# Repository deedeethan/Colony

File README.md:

Colony
======

**General Body Meeting: Thursdays at 5:30pm in WEH 5312**
- Mechanical: Saturdays 1pm in Roboclub
  - contact Jason Dynes (jdynes@andrew.cmu.edu)
- Electrical: Saturdays 1pm in Roboclub
  - contact Jess Chernak (jchernak@andrew.cmu.edu)
- Low Level: Saturdays 3:30pm in Roboclub
  - contact Tom Mullins (tmullins@andrew.cmu.edu)
- High Level: Thursdays after GBM (6:00pm) in WEH 5312
  - contact Tim Brown (twbrown@andrew.cmu.edu)

Contact: [aperley@andrew.cmu.edu](mailto:aperley@andrew.cmu.edu), [jchernak@andrew.cmu.edu](mailto:jchernak@andrew.cmu.edu)

[Wiki](https://github.com/CMU-Robotics-Club/Colony/wiki)
--------------------------------------------------------

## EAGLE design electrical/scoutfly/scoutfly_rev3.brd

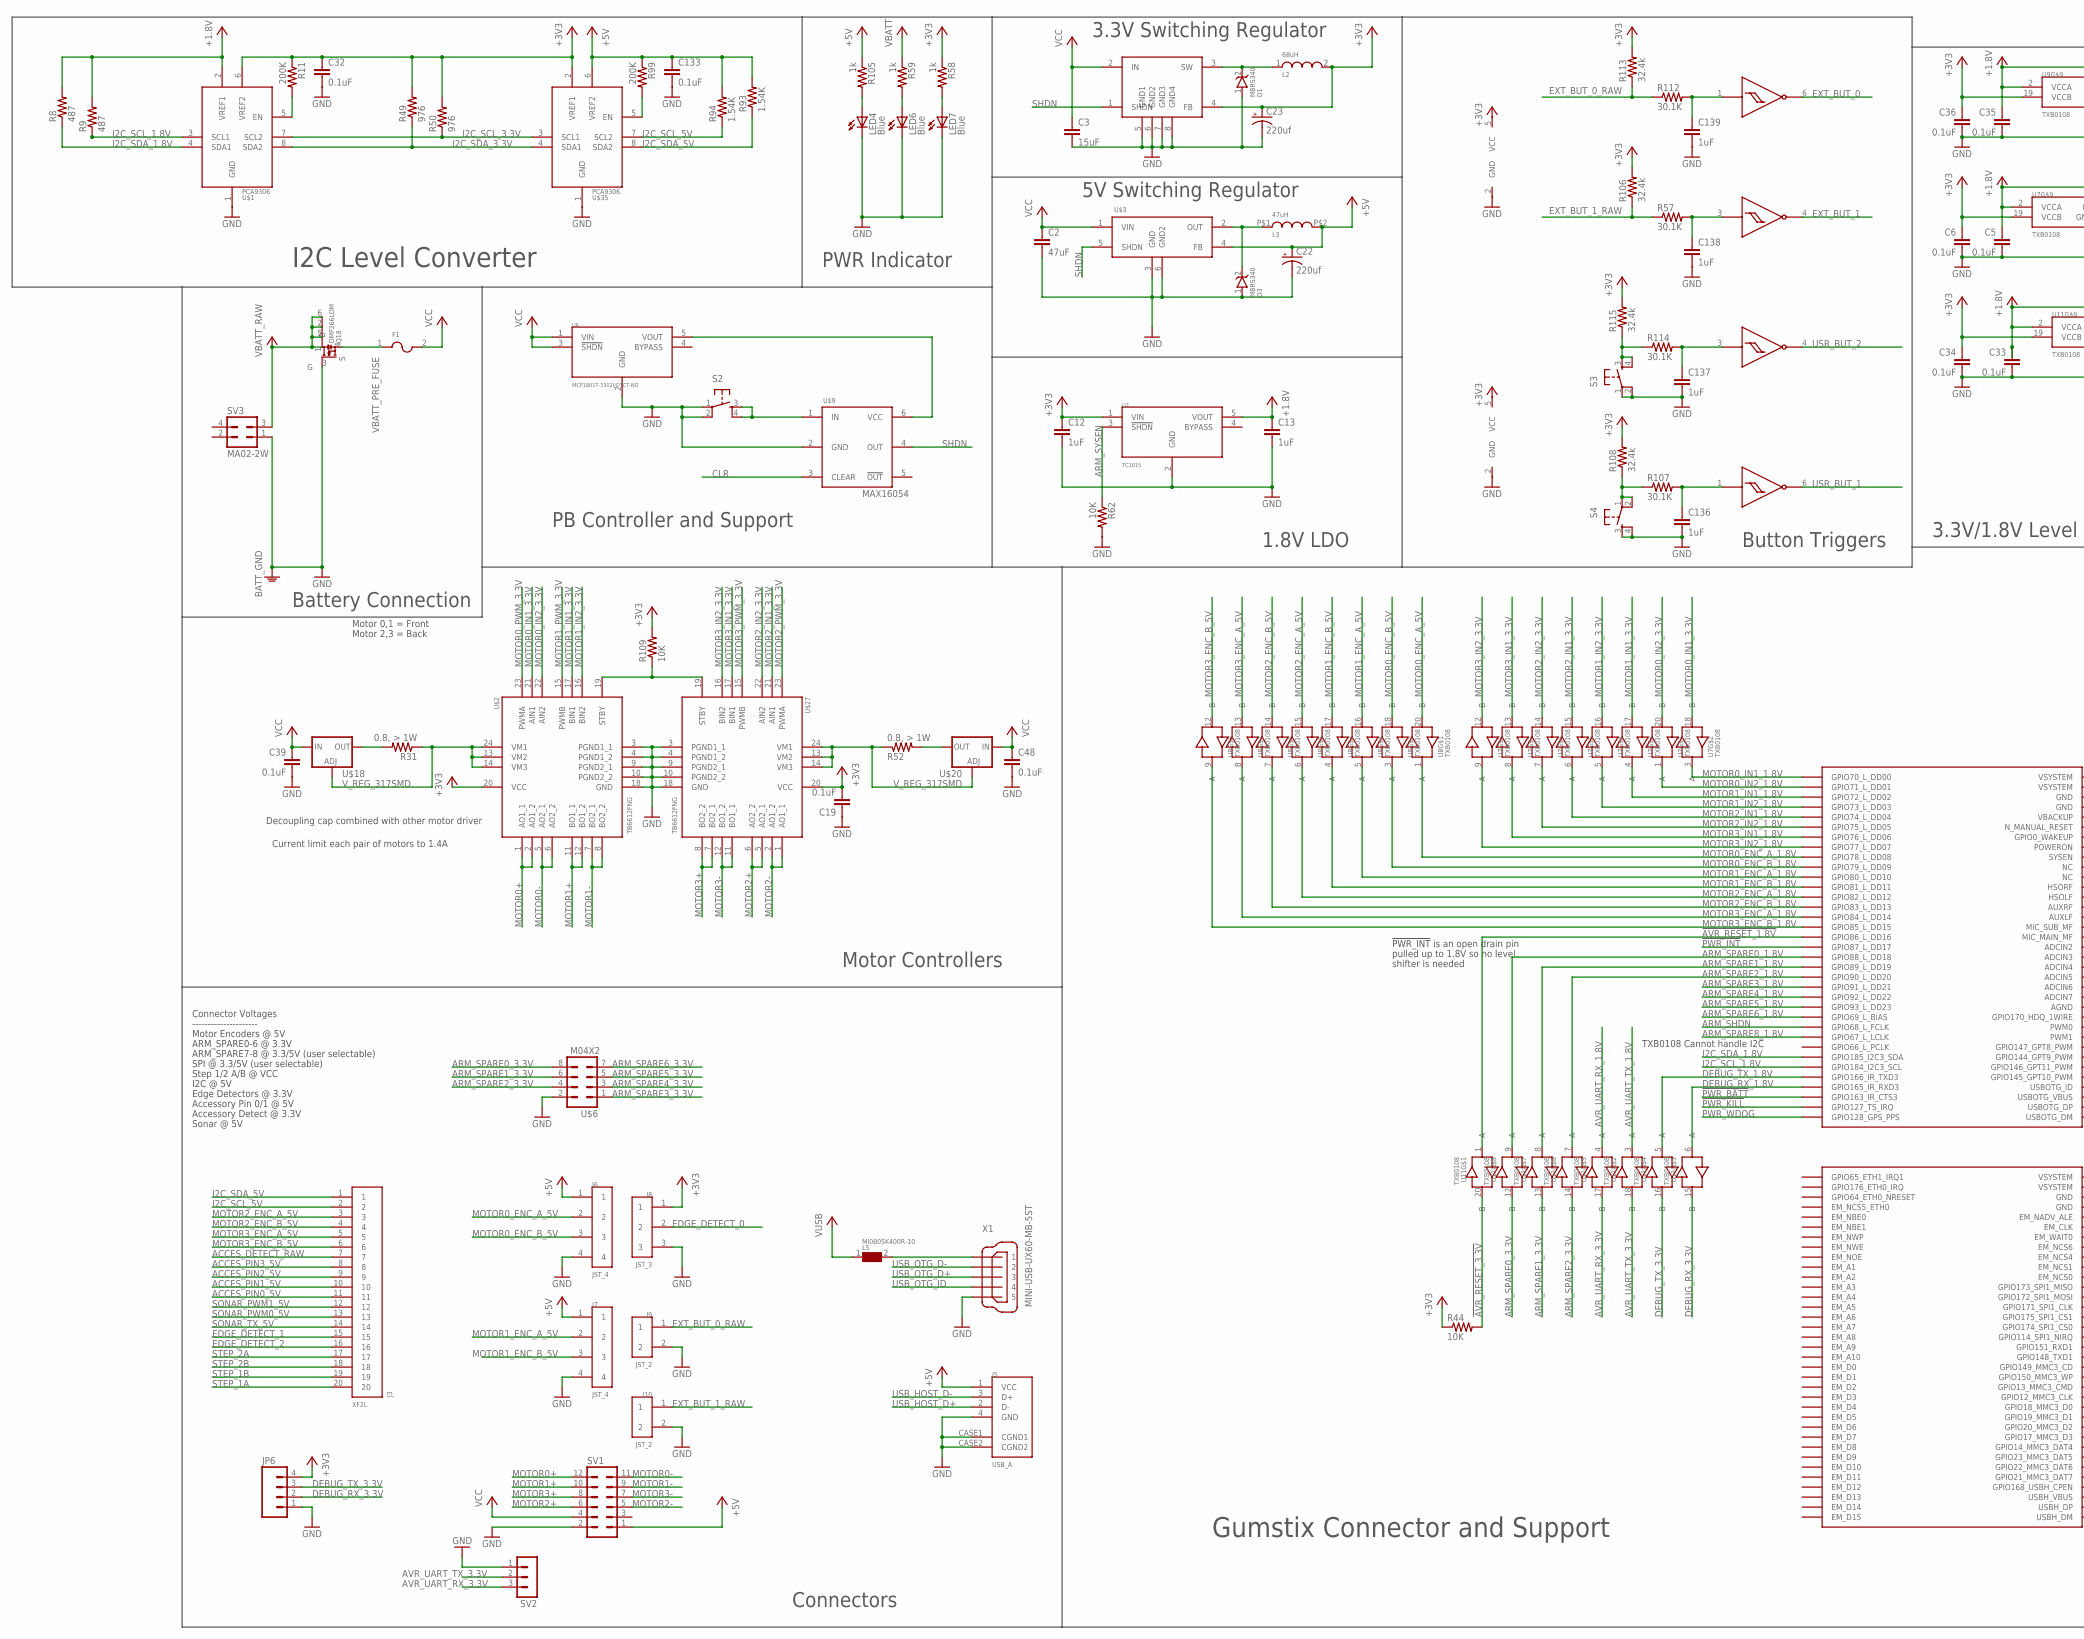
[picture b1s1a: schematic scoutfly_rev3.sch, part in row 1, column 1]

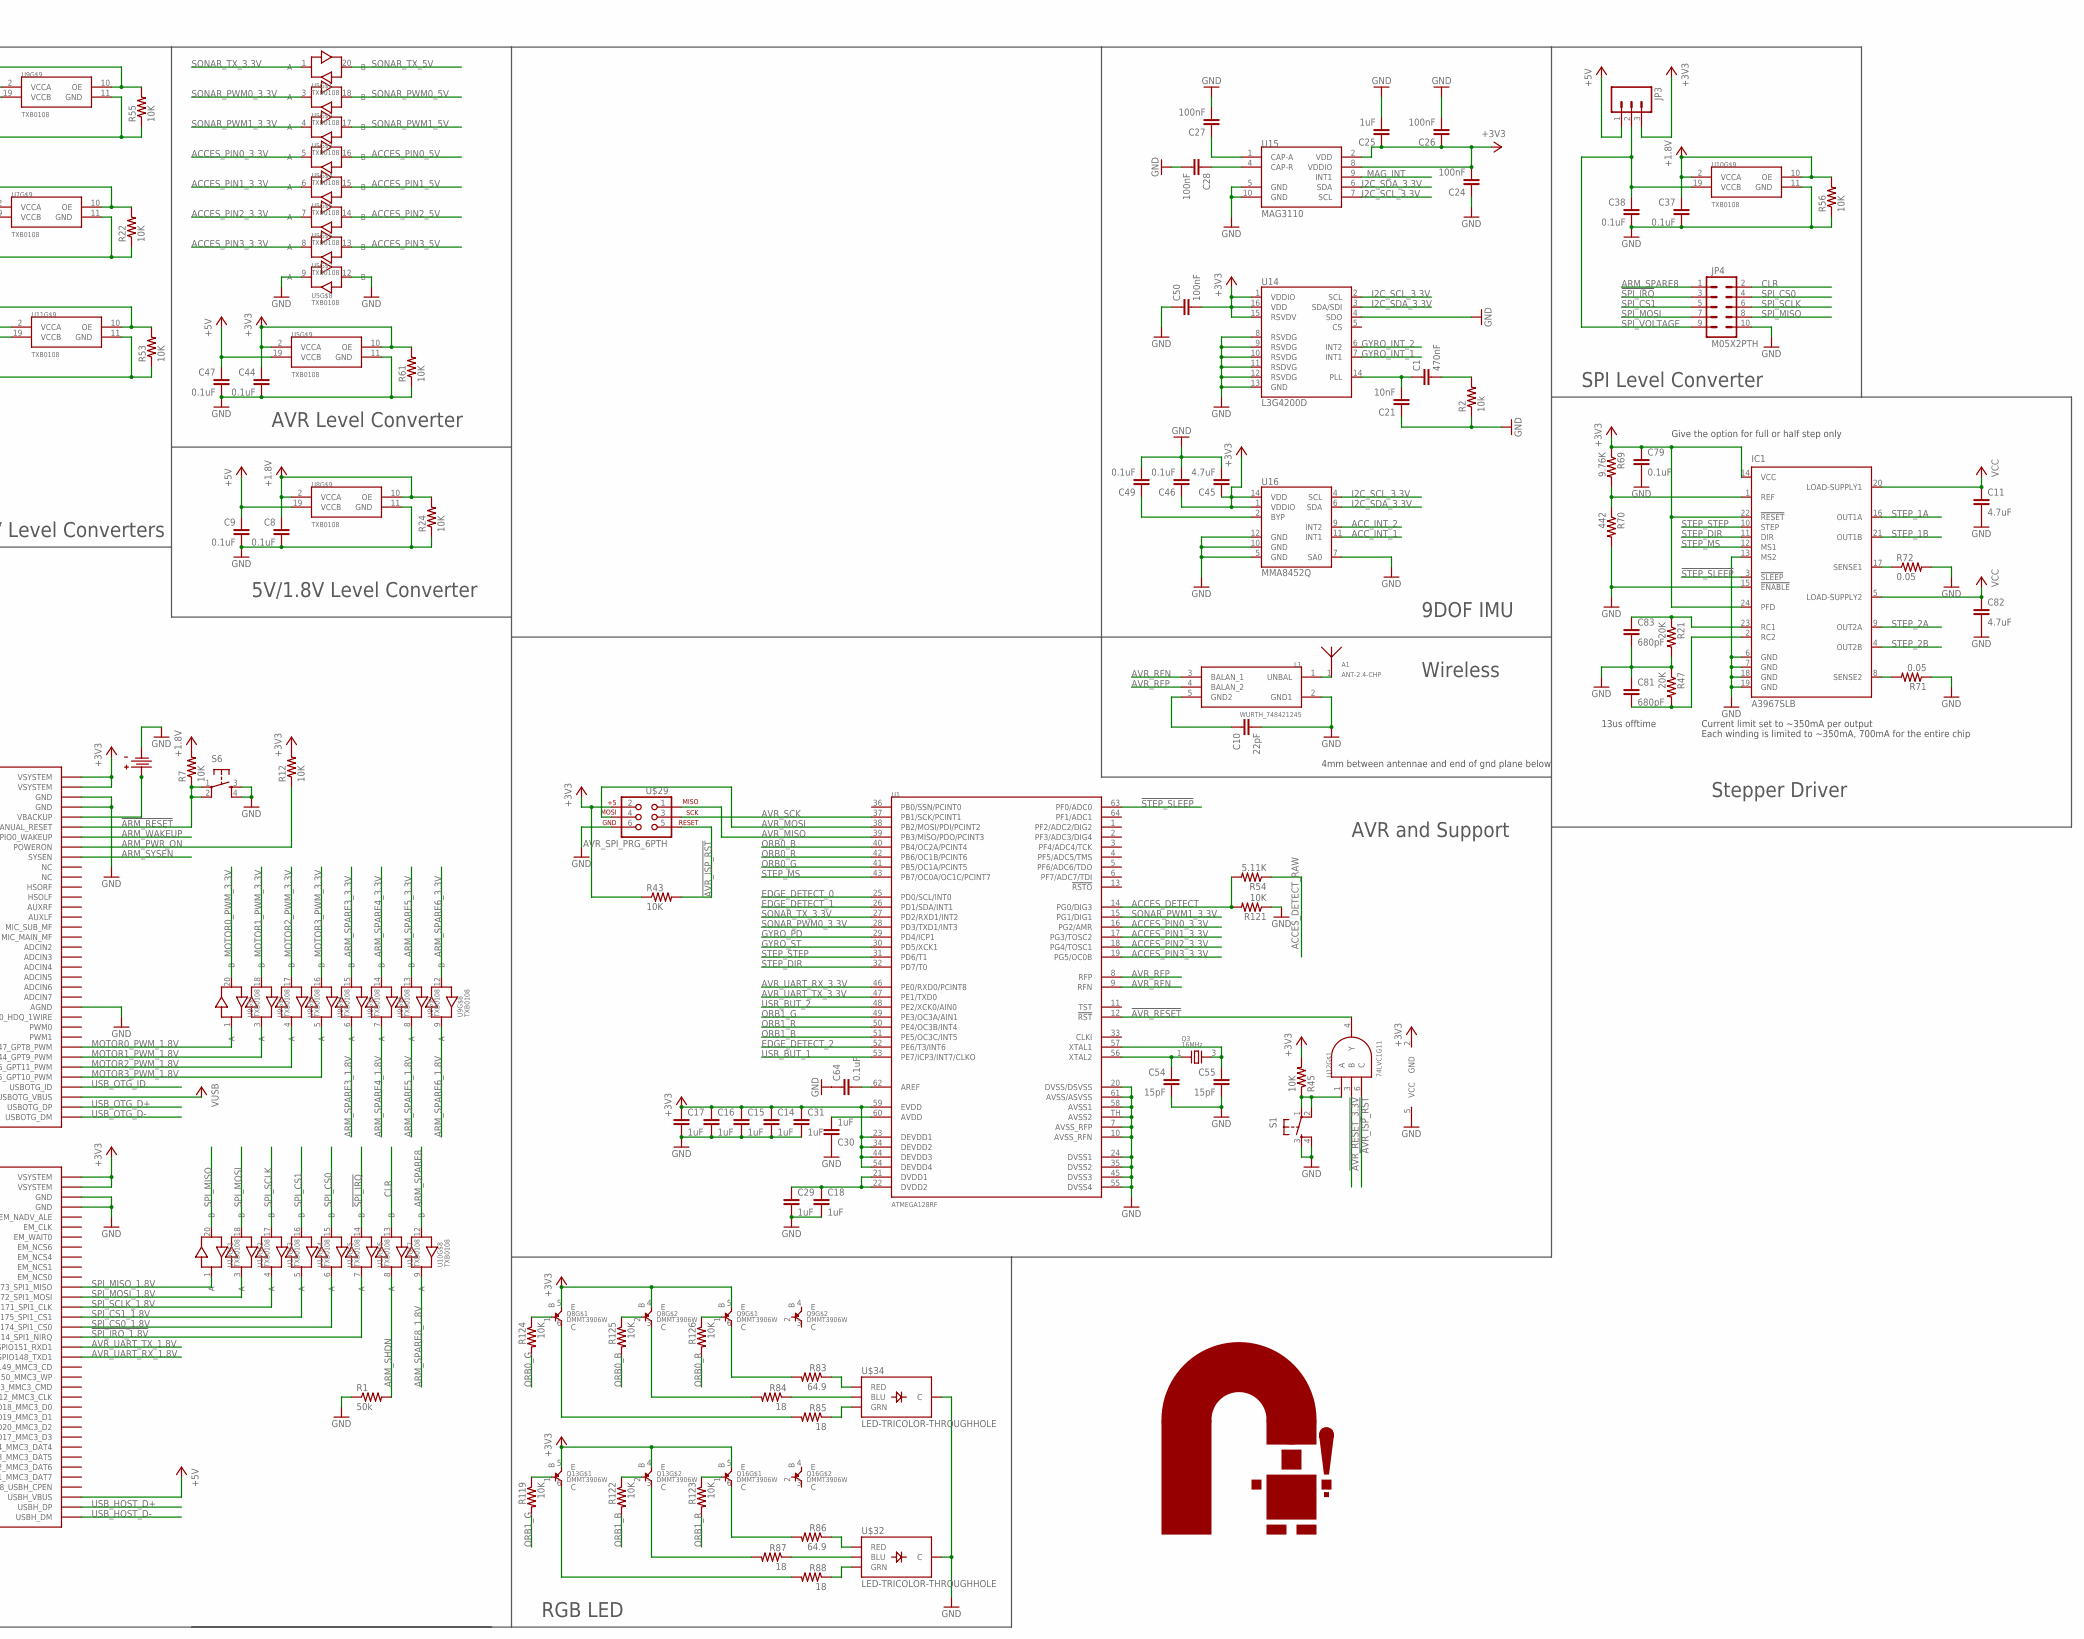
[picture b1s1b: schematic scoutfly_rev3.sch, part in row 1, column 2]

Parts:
A1: ANT-2.4-CHP; CHIP_ANT_2.4GHZ
C1: 470nF; 0603-CAP
C2: 47uF; 0805
C3: 15uF; 0603-CAP
C5, C6, C8, C9, C19, C32, C33, C34, C35, C36, C37, C38, C39, C44, C46, C47, C48, C49, C64, C79, C133: 0.1uF; 0603-CAP
C10: 22pF; 0603-CAP
C11, C82: 4.7uF; C0805
C12, C13, C14, C15, C16, C17, C18, C25, C29, C30, C31, C136, C137, C138, C139: 1uF; 0603-CAP
C21: 10nF; 0603-CAP
C22, C23: 220uf; CT6032
C24, C26, C27, C28, C50: 100nF; 0603-CAP
C45: 4.7uF; 0603-CAP
C54, C55: 15pF; 0603-CAP
C81, C83: 680pF; 0603-CAP
D1, D3: MBRS340; SMC/DO-214AB
F1: MF-SM200; SM200
IC1: A3967SLB; SO24W
J3: XF2L; OMRON_XF
J5: USB_A
J6, J7: JST_4; JST_ZH_4
J8: JST_3; JST_ZH_3
J9, J10: JST_2; JST_ZH_2
J12: KEYSTONE_3000; COIN_CELL
JP3: M03PTH; 1X03
JP4: M05X2PTH; AVR_ICSP
JP6: M04LOCK; 1X04_LOCK
L1: WURTH_748421245; WURTH_BALUN
L2: 68uH; NR6045
L3: 47uH; 0.492L0.492W0.236HINDUCTOR
L5: MI0805K400R-10; 0805
LED4, LED6, LED7: Blue; LED-0603
Q3: 16MHz; NX3225SA
Q8, Q9, Q13, Q16: DMMT3906W; SOT363
Q18: DMP266LDM; SOT26
R1: 50k; R0603
R2: 10k; R0603
R7, R12, R22, R24, R43, R44, R45, R53, R55, R56, R61, R62, R109, R119, R121, R122, R123, R124, R125, R126: 10K; R0603
R8, R9: 487; R0603
R11, R99: 200K; R0603
R21, R47: 20K; R0603
R31, R52: 0.8, > 1W; R2512
R49, R50: 976; R0603
R54: 5.11K; R0603
R57, R107, R112, R114: 30.1K; R0603
R58, R59, R105: 1k; R0603
R69: 9.76K; R0603
R70: 442; R0603
R71, R72: 0.05; R0603
R83, R86: 64.9; R0603
R84, R85, R87, R88: 18; R0603
R93, R94: 1.54K; R0603
R106, R108, R113, R115: 32.4k; R0603
S1, S2, S3, S4, S6: TAC_SWITCHSMD; TACTILE_SWITCH_SMD
SV1: MA06-2W
SV2: MA03-1
SV3: MA02-2W
U1: ATMEGA128RF; MLF64-TH
U2: TC1015; 5-SOT23
U3, U4: NL27WZ14; SOT363
U5, U7, U8, U9, U10, U11: TXB0108; 20-TSSOP
U6: MCP1801T-3302I/OTCT-ND; 5-SOT23
U12: 74LVC1G11; 6-SOT23
U14: L3G4200D; LGA16-4X4
U15: MAG3110; DFN-10
U16: MMA8452Q; QFN-16_0.5MM
U$1, U$35: PCA9306; TSSOP8
U$2, U$27: TB6612FNG; 24-SSOP
U$3: AP1501; DD2PAK
U$6: M04X2; 2X4
U$7: ROBOLOGOSILKSCREEN; RCLOGO
U$9: MAX16054; 6-TSOT23
U$10: MIC4680-3.3YM; 8-SOIC
U$16: OVERO
U$18, U$20: V_REG_317SMD; SOT223
U$29: AVR_SPI_PRG_6PTH; 2X3
U$32, U$34: LED-TRICOLOR-THROUGHHOLE
X1: MINI-USB-UX60-MB-5ST; UX60-MB-5ST

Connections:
!ARM_RESET: R7.1, S6.1, S6.2, U$16.N_MANUAL_RESET
!AVR_ISP_RST: R43.2, U12.6 (C), U$29.5
!AVR_RESET: U1.12 (!RST), U12.4 (Y)
!AVR_RESET_1.8V: U11.1 (A), U$16.GPIO86_L_DD16
!AVR_RESET_3.3V: R44.2, U11.20 (B), U12.3 (B)
!PWR_BATT: U$16.GPIO163_IR_CTS3
!PWR_INT: U$16.GPIO87_L_DD17
!PWR_KILL: U$16.GPIO127_TS_IRQ
!SPI_IRQ: JP4.3, U10.14 (B)
!SPI_IRQ_1.8V: U10.7 (A), U$16.GPIO114_SPI1_NIRQ
!STEP_SLEEP: IC1.3 (!SLEEP), U1.63 (PF0/ADC0)
+1.8V: C5.1, C8.1, C13.1, C33.1, C35.1, C37.1, R7.2, R8.2, R9.2, R22.2, R24.2, R53.2, R55.2, R56.2, U2.5 (VOUT), U7.2 (VCCA), U7.10 (OE), U8.2 (VCCA), U8.10 (OE), U9.2 (VCCA), U9.10 (OE), U10.2 (VCCA), U10.10 (OE), U11.2 (VCCA), U11.10 (OE), U$1.2 (VREF1)
+3V3: C6.1, C12.1, C14.1, C15.1, C16.1, C17.1, C19.2, C23.+, C24.2, C25.1, C26.1, C31.1, C32.1, C34.1, C36.1, C44.1, C45.1, C46.1, C50.2, C79.1, IC1.14 (VCC), IC1.22 (!RESET), IC1.24 (PFD), J8.1, JP3.3, JP6.4, L2.2, Q8.4 (E), Q8.5 (E), Q9.5 (E), Q13.4 (E), Q13.5 (E), Q16.5 (E), R11.1, R12.2, R43.1, R44.1, R45.2, R49.2, R50.2, R58.1, R61.2, R69.1, R106.2, R108.2, R109.2, R113.2, R115.2, U1.23 (DEVDD1), U1.34 (DEVDD2), U1.44 (DEVDD3), U1.54 (DEVDD4), U1.59 (EVDD), U2.1 (VIN), U3.5 (VCC), U4.5 (VCC), U5.2 (VCCA), U5.10 (OE), U7.19 (VCCB), U9.19 (VCCB), U11.19 (VCCB), U12.2 (GND), U14.1 (VDDIO), U14.15 (RSVDV), U14.16 (VDD), U15.2 (VDD), U15.8 (VDDIO), U16.1 (VDDIO), U16.14 (VDD), U$1.6 (VREF2), U$2.20 (VCC), U$10.4 (FB), U$16.VSYSTEM@1 (VSYSTEM), U$16.VSYSTEM@2 (VSYSTEM), U$16.VSYSTEM@66 (VSYSTEM), U$16.VSYSTEM@67 (VSYSTEM), U$27.20 (VCC), U$29.2, U$35.2 (VREF1)
+5V: C9.1, C22.+, C47.1, C133.1, J5.1 (VCC), J6.1, J7.1, JP3.1, L3.P$2 (2), R93.2, R94.2, R99.1, R105.1, SV1.1, U5.19 (VCCB), U8.19 (VCCB), U$3.4 (FB), U$16.USBH_VBUS, U$35.6 (VREF2)
ACCES_DETECT: R54.2, R121.2, U1.14 (PG0/DIG3)
ACCES_DETECT_RAW: J3.7, R54.1
ACCES_PIN0_3.3V: U1.16 (PG2/AMR), U5.5 (A)
ACCES_PIN0_5V: J3.11, U5.16 (B)
ACCES_PIN1_3.3V: U1.17 (PG3/TOSC2), U5.6 (A)
ACCES_PIN1_5V: J3.10, U5.15 (B)
ACCES_PIN2_3.3V: U1.18 (PG4/TOSC1), U5.7 (A)
ACCES_PIN2_5V: J3.9, U5.14 (B)
ACCES_PIN3_3.3V: U1.19 (PG5/OC0B), U5.8 (A)
ACCES_PIN3_5V: J3.8, U5.13 (B)
ACC_INT_1: U16.11 (INT1)
ACC_INT_2: U16.9 (INT2)
ARM_PWR_ON: R12.1, U$16.POWERON
ARM_SHDN: R1.2, U10.8 (A), U$16.GPIO68_L_FCLK
ARM_SPARE0_1.8V: U11.9 (A), U$16.GPIO88_L_DD18
ARM_SPARE0_3.3V: U11.12 (B), U$6.8
ARM_SPARE1_1.8V: U11.8 (A), U$16.GPIO89_L_DD19
ARM_SPARE1_3.3V: U11.13 (B), U$6.6
ARM_SPARE2_1.8V: U11.7 (A), U$16.GPIO90_L_DD20
ARM_SPARE2_3.3V: U11.14 (B), U$6.4
ARM_SPARE3_1.8V: U9.6 (A), U$16.GPIO91_L_DD21
ARM_SPARE3_3.3V: U9.15 (B), U$6.1
ARM_SPARE4_1.8V: U9.7 (A), U$16.GPIO92_L_DD22
ARM_SPARE4_3.3V: U9.14 (B), U$6.3
ARM_SPARE5_1.8V: U9.8 (A), U$16.GPIO93_L_DD23
ARM_SPARE5_3.3V: U9.13 (B), U$6.5
ARM_SPARE6_1.8V: U9.9 (A), U$16.GPIO69_L_BIAS
ARM_SPARE6_3.3V: U9.12 (B), U$6.7
ARM_SPARE8: JP4.1, U10.12 (B)
ARM_SPARE8_1.8V: U10.9 (A), U$16.GPIO67_L_LCLK
ARM_SYSEN: R62.1, U2.3 (!SHDN), U$16.SYSEN
ARM_WAKEUP: U$16.GPIO0_WAKEUP
AVR_MISO: U1.39 (PB3/MISO/PDO/PCINT3), U$29.1
AVR_MOSI: U1.38 (PB2/MOSI/PDI/PCINT2), U$29.4
AVR_RFN: L1.3 (BALAN_1), U1.9 (RFN)
AVR_RFP: L1.4 (BALAN_2), U1.8 (RFP)
AVR_SCK: U1.37 (PB1/SCK/PCINT1), U$29.3
AVR_UART_RX_1.8V: U11.4 (A), U$16.GPIO148_TXD1
AVR_UART_RX_3.3V: SV2.3, U1.46 (PE0/RXD0/PCINT8), U11.17 (B)
AVR_UART_TX_1.8V: U11.3 (A), U$16.GPIO151_RXD1
AVR_UART_TX_3.3V: SV2.2, U1.47 (PE1/TXD0), U11.18 (B)
CLR: JP4.2, U10.13 (B), U$9.3 (CLEAR)
DEBUG_RX_1.8V: U11.6 (A), U$16.GPIO165_IR_RXD3
DEBUG_RX_3.3V: JP6.2, U11.15 (B)
DEBUG_TX_1.8V: U11.5 (A), U$16.GPIO166_IR_TXD3
DEBUG_TX_3.3V: JP6.3, U11.16 (B)
EDGE_DETECT_0: J8.2, U1.25 (PD0/SCL/INT0)
EDGE_DETECT_1: J3.15, U1.26 (PD1/SDA/INT1)
EDGE_DETECT_2: J3.16, U1.52 (PE6/T3/INT6)
EXT_BUT_0: U3.6 (Y)
EXT_BUT_0_RAW: J9.1, R112.1, R113.1
EXT_BUT_1: U3.4 (Y)
EXT_BUT_1_RAW: J10.1, R57.1, R106.1
GND: C2.2, C3.2, C5.2, C6.2, C8.2, C9.2, C10.2, C11.2, C12.2, C13.2, C14.2, C15.2, C16.2, C17.2, C18.2, C19.1, C21.1, C22.-, C23.-, C24.1, C25.2, C26.2, C27.2, C28.2, C29.2, C30.1, C31.2, C32.2, C33.2, C34.2, C35.2, C36.2, C37.2, C38.2, C39.2, C44.2, C45.2, C46.2, C47.2, C48.2, C49.2, C50.1, C54.2, C55.2, C64.1, C79.2, C81.1, C82.2, C83.2, C133.2, C136.2, C137.2, C138.2, C139.2, D1.1, D3.1, IC1.6 (GND), IC1.7 (GND), IC1.13 (MS2), IC1.15 (!ENABLE), IC1.18 (GND), IC1.19 (GND), J5.4 (GND), J5.CASE1 (CGND1), J5.CASE2 (CGND2), J6.4, J7.4, J8.3, J9.2, J10.2, J12.NEGATIVE (-), JP4.10, JP6.1, L1.2 (GND1), LED4.C, LED6.C, LED7.C, Q18.3 (G), R1.1, R2.1, R21.2, R22.1, R24.1, R47.1, R53.1, R55.1, R56.1, R61.1, R62.2, R70.2, R71.1, R72.2, R121.1, S1.3, S1.4, S2.1, S2.2, S3.1, S3.2, S4.3, S4.4, S6.3, S6.4, SV1.2, SV2.1, SV3.1, U1.7 (AVSS_RFP), U1.10 (AVSS_RFN), U1.20 (DVSS/DSVSS), U1.24 (DVSS1), U1.35 (DVSS2), U1.45 (DVSS3), U1.55 (DVSS4), U1.58 (AVSS1), U1.61 (AVSS/ASVSS), U1.TH (AVSS2), U2.2 (GND), U3.2 (GND), U4.2 (GND), U5.9 (A), U5.11 (GND), U5.12 (B), U6.2 (GND), U7.11 (GND), U8.11 (GND), U9.11 (GND), U10.11 (GND), U11.11 (GND), U12.5 (VCC), U14.4 (SDO), U14.8 (RSVDG), U14.9 (RSVDG), U14.10 (RSVDG), U14.11 (RSDVG), U14.12 (RSVDG), U14.13 (GND), U15.5 (GND), U15.10 (GND), U16.5 (GND), U16.7 (SA0), U16.10 (GND), U16.12 (GND), U$1.1 (GND), U$2.3 (PGND1_1), U$2.4 (PGND1_2), U$2.9 (PGND2_1), U$2.10 (PGND2_2), U$2.18 (GND), U$3.3 (GND), U$3.6 (GND2), U$6.2, U$9.2 (GND), U$10.5 (GND1), U$10.6 (GND2), U$10.7 (GND3), U$10.8 (GND4), U$16.AGND, U$16.GND, U$16.GND@33 (GND), U$16.GND@56 (GND), U$16.GND@70 (GND), U$27.3 (PGND1_1), U$27.4 (PGND1_2), U$27.9 (PGND2_1), U$27.10 (PGND2_2), U$27.18 (GND), U$29.6, U$32.GND (C), U$34.GND (C), U$35.1 (GND), X1.5
GYRO_INT_1: U14.7 (INT1)
GYRO_INT_2: U14.6 (INT2)
GYRO_PD: U1.29 (PD4/ICP1)
GYRO_ST: U1.30 (PD5/XCK1)
I2C_SCL_1.8V: R9.1, U$1.3 (SCL1), U$16.GPIO184_I2C3_SCL
I2C_SCL_3.3V: R50.1, U14.2 (SCL), U15.7 (SCL), U16.4 (SCL), U$1.7 (SCL2), U$35.3 (SCL1)
I2C_SCL_5V: J3.2, R94.1, U$35.7 (SCL2)
I2C_SDA_1.8V: R8.1, U$1.4 (SDA1), U$16.GPIO185_I2C3_SDA
I2C_SDA_3.3V: R49.1, U14.3 (SDA/SDI), U15.6 (SDA), U16.6 (SDA), U$1.8 (SDA2), U$35.4 (SDA1)
I2C_SDA_5V: J3.1, R93.1, U$35.8 (SDA2)
MAG_INT: U15.9 (INT1)
MOTOR0+: SV1.12, U$2.1 (AO1_1), U$2.2 (AO1_2)
MOTOR0-: SV1.11, U$2.5 (AO2_1), U$2.6 (AO2_2)
MOTOR0_ENC_A_1.8V: U8.1 (A), U$16.GPIO78_L_DD08
MOTOR0_ENC_A_5V: J6.2, U8.20 (B)
MOTOR0_ENC_B_1.8V: U8.3 (A), U$16.GPIO79_L_DD09
MOTOR0_ENC_B_5V: J6.3, U8.18 (B)
MOTOR0_IN1_1.8V: U7.3 (A), U$16.GPIO70_L_DD00
MOTOR0_IN1_3.3V: U7.18 (B), U$2.21 (AIN1)
MOTOR0_IN2_1.8V: U7.1 (A), U$16.GPIO71_L_DD01
MOTOR0_IN2_3.3V: U7.20 (B), U$2.22 (AIN2)
MOTOR0_PWM_1.8V: U9.1 (A), U$16.GPIO147_GPT8_PWM
MOTOR0_PWM_3.3V: U9.20 (B), U$2.23 (PWMA)
MOTOR1+: SV1.10, U$2.11 (BO1_1), U$2.12 (BO1_2)
MOTOR1-: SV1.9, U$2.7 (BO2_1), U$2.8 (BO2_2)
MOTOR1_ENC_A_1.8V: U8.5 (A), U$16.GPIO80_L_DD10
MOTOR1_ENC_A_5V: J7.2, U8.16 (B)
MOTOR1_ENC_B_1.8V: U8.4 (A), U$16.GPIO81_L_DD11
MOTOR1_ENC_B_5V: J7.3, U8.17 (B)
MOTOR1_IN1_1.8V: U7.4 (A), U$16.GPIO72_L_DD02
MOTOR1_IN1_3.3V: U7.17 (B), U$2.17 (BIN1)
MOTOR1_IN2_1.8V: U7.5 (A), U$16.GPIO73_L_DD03
MOTOR1_IN2_3.3V: U7.16 (B), U$2.16 (BIN2)
MOTOR1_PWM_1.8V: U9.3 (A), U$16.GPIO144_GPT9_PWM
MOTOR1_PWM_3.3V: U9.18 (B), U$2.15 (PWMB)
MOTOR2+: SV1.6, U$27.5 (AO2_1), U$27.6 (AO2_2)
MOTOR2-: SV1.5, U$27.1 (AO1_1), U$27.2 (AO1_2)
MOTOR2_ENC_A_1.8V: U8.6 (A), U$16.GPIO82_L_DD12
MOTOR2_ENC_A_5V: J3.3, U8.15 (B)
MOTOR2_ENC_B_1.8V: U8.7 (A), U$16.GPIO83_L_DD13
MOTOR2_ENC_B_5V: J3.4, U8.14 (B)
MOTOR2_IN1_1.8V: U7.6 (A), U$16.GPIO74_L_DD04
MOTOR2_IN1_3.3V: U7.15 (B), U$27.21 (AIN1)
MOTOR2_IN2_1.8V: U7.7 (A), U$16.GPIO75_L_DD05
MOTOR2_IN2_3.3V: U7.14 (B), U$27.22 (AIN2)
MOTOR2_PWM_1.8V: U9.4 (A), U$16.GPIO146_GPT11_PWM
MOTOR2_PWM_3.3V: U9.17 (B), U$27.23 (PWMA)
MOTOR3+: SV1.8, U$27.7 (BO2_1), U$27.8 (BO2_2)
MOTOR3-: SV1.7, U$27.11 (BO1_1), U$27.12 (BO1_2)
MOTOR3_ENC_A_1.8V: U8.8 (A), U$16.GPIO84_L_DD14
MOTOR3_ENC_A_5V: J3.5, U8.13 (B)
MOTOR3_ENC_B_1.8V: U8.9 (A), U$16.GPIO85_L_DD15
MOTOR3_ENC_B_5V: J3.6, U8.12 (B)
MOTOR3_IN1_1.8V: U7.8 (A), U$16.GPIO76_L_DD06
MOTOR3_IN1_3.3V: U7.13 (B), U$27.17 (BIN1)
MOTOR3_IN2_1.8V: U7.9 (A), U$16.GPIO77_L_DD07
MOTOR3_IN2_3.3V: U7.12 (B), U$27.16 (BIN2)
MOTOR3_PWM_1.8V: U9.5 (A), U$16.GPIO145_GPT10_PWM
MOTOR3_PWM_3.3V: U9.16 (B), U$27.15 (PWMB)
unnamed: A1.1, L1.1 (UNBAL)
unnamed: R45.1, S1.1, S1.2, U12.1 (A)
unnamed: J12.PLUS1 (+), J12.PLUS2 (+2), U$16.VBACKUP
unnamed: C83.1, IC1.23 (RC1), R21.1
unnamed: IC1.17 (SENSE1), R72.1
unnamed: IC1.8 (SENSE2), R71.2
unnamed: C81.2, IC1.2 (RC2), R47.2
unnamed: C10.1, L1.5 (GND2)
unnamed: Q8.1 (B), R124.1
unnamed: D1.2, L2.1, U$10.3 (SW)
unnamed: C30.2, U1.60 (AVDD)
unnamed: D3.2, L3.P$1 (1), U$3.2 (OUT)
unnamed: C18.1, C29.1, U1.21 (DVDD1), U1.22 (DVDD2)
unnamed: R11.2, U$1.5 (EN)
unnamed: C64.2, U1.62 (AREF)
unnamed: R31.1, U$2.13 (VM2), U$2.14 (VM3), U$2.24 (VM1), U$18.1 (ADJ)
unnamed: R31.2, U$18.2 (OUT)
unnamed: R52.1, U$20.1 (ADJ), U$27.13 (VM2), U$27.14 (VM3), U$27.24 (VM1)
unnamed: R52.2, U$20.2 (OUT)
unnamed: C1.1, C21.2, U14.14 (PLL)
unnamed: C1.2, R2.2
unnamed: Q8.2 (B), R125.1
unnamed: Q9.1 (B), R126.1
unnamed: Q16.1 (B), R123.1
unnamed: Q13.2 (B), R122.1
unnamed: Q13.1 (B), R119.1
unnamed: S2.3, S2.4, U$9.1 (IN)
unnamed: U6.5 (VOUT), U$9.6 (VCC)
unnamed: R85.1, U$34.GRN
unnamed: C49.1, U16.2 (BYP)
unnamed: C27.1, U15.1 (CAP-A)
unnamed: C28.1, U15.4 (CAP-R)
unnamed: L5.2, X1.1
unnamed: C55.1, Q3.3 (2), U1.57 (XTAL1)
unnamed: C54.1, Q3.1, U1.56 (XTAL2)
unnamed: C138.1, R57.2, U3.3 (X)
unnamed: IC1.1 (REF), R69.2, R70.1
unnamed: R109.1, U$2.19 (STBY), U$27.19 (STBY)
unnamed: R84.1, U$34.BLU
unnamed: R83.1, U$34.RED
unnamed: Q9.6 (C), R83.2
unnamed: Q8.3 (C), R84.2
unnamed: Q8.6 (C), R85.2
unnamed: R88.1, U$32.GRN
unnamed: R87.1, U$32.BLU
unnamed: R86.1, U$32.RED
unnamed: Q16.6 (C), R86.2
unnamed: Q13.3 (C), R87.2
unnamed: Q13.6 (C), R88.2
unnamed: R99.2, U$35.5 (EN)
unnamed: LED4.A, R105.2
unnamed: LED6.A, R59.2
unnamed: LED7.A, R58.2
unnamed: C139.1, R112.2, U3.1 (X)
unnamed: C137.1, R114.2, U4.3 (X)
unnamed: C136.1, R107.2, U4.1 (X)
unnamed: R107.1, R108.1, S4.1, S4.2
unnamed: R114.1, R115.1, S3.3, S3.4
ORB0_B: R125.2, U1.40 (PB4/OC2A/PCINT4)
ORB0_G: R124.2, U1.41 (PB5/OC1A/PCINT5)
ORB0_R: R126.2, U1.42 (PB6/OC1B/PCINT6)
ORB1_B: R122.2, U1.51 (PE5/OC3C/INT5)
ORB1_G: R119.2, U1.49 (PE3/OC3A/AIN1)
ORB1_R: R123.2, U1.50 (PE4/OC3B/INT4)
PWR_WDOG: U$16.GPIO128_GPS_PPS
SHDN: U$3.5 (SHDN), U$9.4 (OUT), U$10.1 (SHDN)
SONAR_PWM0_3.3V: U1.28 (PD3/TXD1/INT3), U5.3 (A)
SONAR_PWM0_5V: J3.13, U5.18 (B)
SONAR_PWM1_3.3V: U1.15 (PG1/DIG1), U5.4 (A)
SONAR_PWM1_5V: J3.12, U5.17 (B)
SONAR_TX_3.3V: U1.27 (PD2/RXD1/INT2), U5.1 (A)
SONAR_TX_5V: J3.14, U5.20 (B)
SPI_CS0: JP4.4, U10.15 (B)
SPI_CS0_1.8V: U10.6 (A), U$16.GPIO174_SPI1_CS0
SPI_CS1: JP4.5, U10.16 (B)
SPI_CS1_1.8V: U10.5 (A), U$16.GPIO175_SPI1_CS1
SPI_MISO: JP4.8, U10.20 (B)
SPI_MISO_1.8V: U10.1 (A), U$16.GPIO173_SPI1_MISO
SPI_MOSI: JP4.7, U10.18 (B)
SPI_MOSI_1.8V: U10.3 (A), U$16.GPIO172_SPI1_MOSI
SPI_SCLK: JP4.6, U10.17 (B)
SPI_SCLK_1.8V: U10.4 (A), U$16.GPIO171_SPI1_CLK
SPI_VOLTAGE: C38.1, JP3.2, JP4.9, U10.19 (VCCB)
STEP_1A: IC1.16 (OUT1A), J3.20
STEP_1B: IC1.21 (OUT1B), J3.19
STEP_2A: IC1.9 (OUT2A), J3.17
STEP_2B: IC1.4 (OUT2B), J3.18
STEP_DIR: IC1.11 (DIR), U1.32 (PD7/T0)
STEP_MS: IC1.12 (MS1), U1.43 (PB7/OC0A/OC1C/PCINT7)
STEP_STEP: IC1.10 (STEP), U1.31 (PD6/T1)
USB_HOST_D+: J5.2 (D-), U$16.USBH_DP
USB_HOST_D-: J5.3 (D+), U$16.USBH_DM
USB_OTG_D+: U$16.USBOTG_DP, X1.3
USB_OTG_D-: U$16.USBOTG_DM, X1.2
USB_OTG_ID: U$16.USBOTG_ID, X1.4
USR_BUT_1: U1.53 (PE7/ICP3/INT7/CLKO), U4.6 (Y)
USR_BUT_2: U1.48 (PE2/XCK0/AIN0), U4.4 (Y)
VBATT: R59.1
VBATT_PRE_FUSE: F1.1, Q18.4 (S)
VBATT_RAW: Q18.1 (D), Q18.2 (D2), Q18.5 (D3), Q18.6 (D4), SV3.3
VCC: C2.1, C3.1, C11.1, C39.1, C48.1, C82.1, F1.2, IC1.5 (LOAD-SUPPLY2), IC1.20 (LOAD-SUPPLY1), SV1.4, U6.1 (VIN), U6.3 (!SHDN), U$3.1 (VIN), U$10.2 (IN), U$18.3 (IN), U$20.3 (IN)
VUSB: L5.1, U$16.USBOTG_VBUS

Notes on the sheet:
Decoupling cap combined with other motor driver
!PWR_INT! is an open drain pin
pulled up to 1.8V so no level
shifter is needed
TXB0108 Cannot handle I2C
Motor Encoders @ 5V
Connector Voltages
---------------------
ARM_SPARE0-6 @ 3.3V
ARM_SPARE7-8 @ 3.3/5V (user selectable)
SPI @ 3.3/5V (user selectable)
Step 1/2 A/B @ VCC
I2C @ 5V
Edge Detectors @ 3.3V
Accessory Pin 0/1 @ 5V
Accessory Detect @ 3.3V
Sonar @ 5V
Current limit each pair of motors to 1.4A
Current limit set to ~350mA per output
4mm between antennae and end of gnd plane below
Motor 0,1 = Front
Motor 2,3 = Back
Each winding is limited to ~350mA, 700mA for the entire chip
13us offtime
Give the option for full or half step only
3.3V Switching Regulator
5V Switching Regulator
9DOF IMU
Wireless
AVR Level Converter
SPI Level Converter
Button Triggers
3.3V/1.8V Level Converters
AVR and Support
1.8V LDO
PWR Indicator
5V/1.8V Level Converter
RGB LED
Stepper Driver
Gumstix Connector and Support

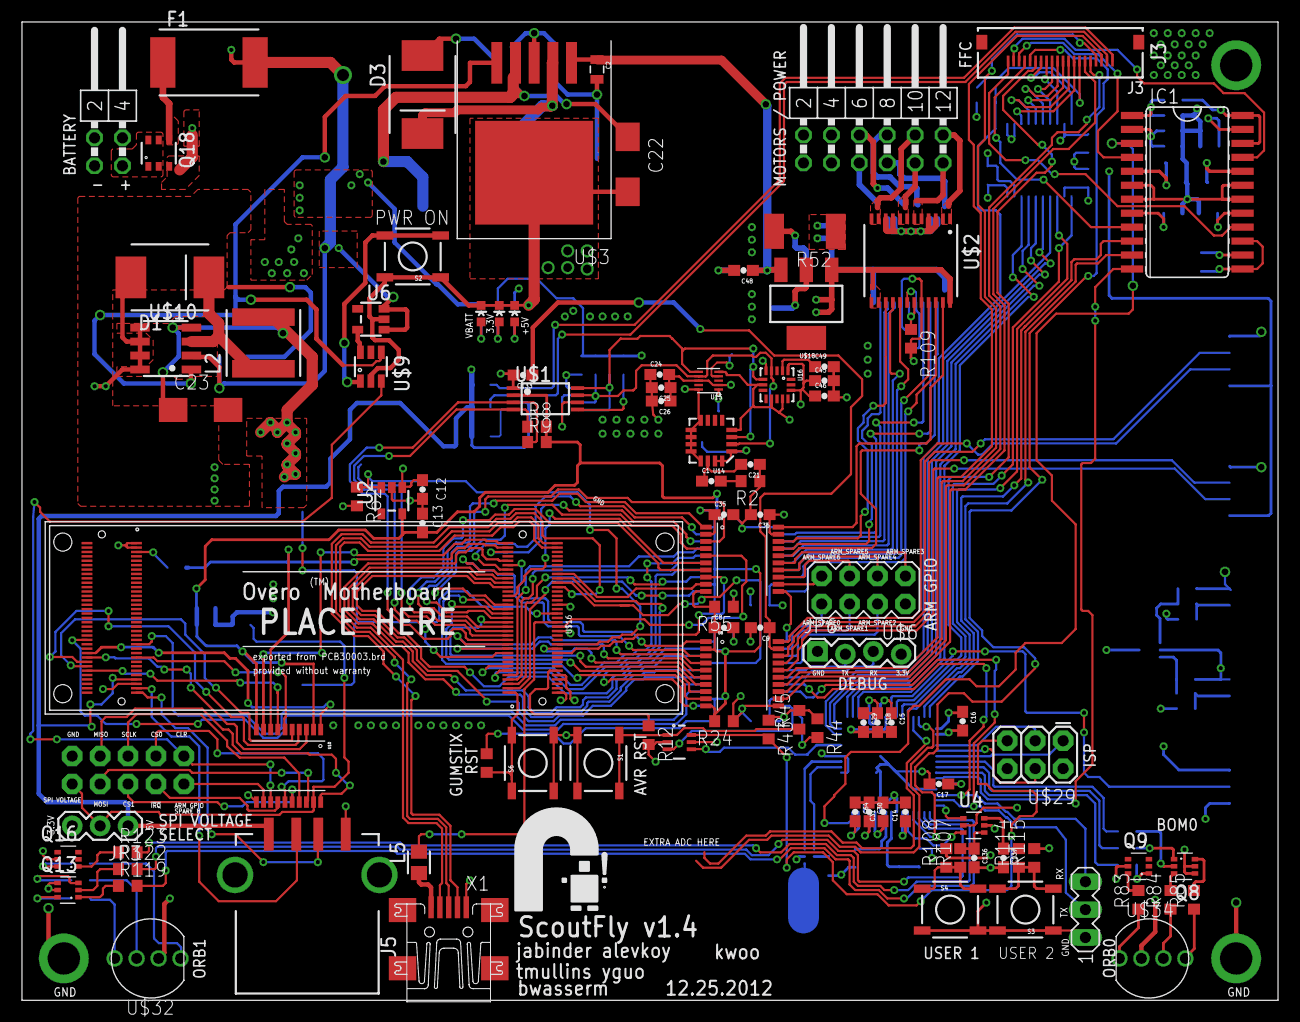
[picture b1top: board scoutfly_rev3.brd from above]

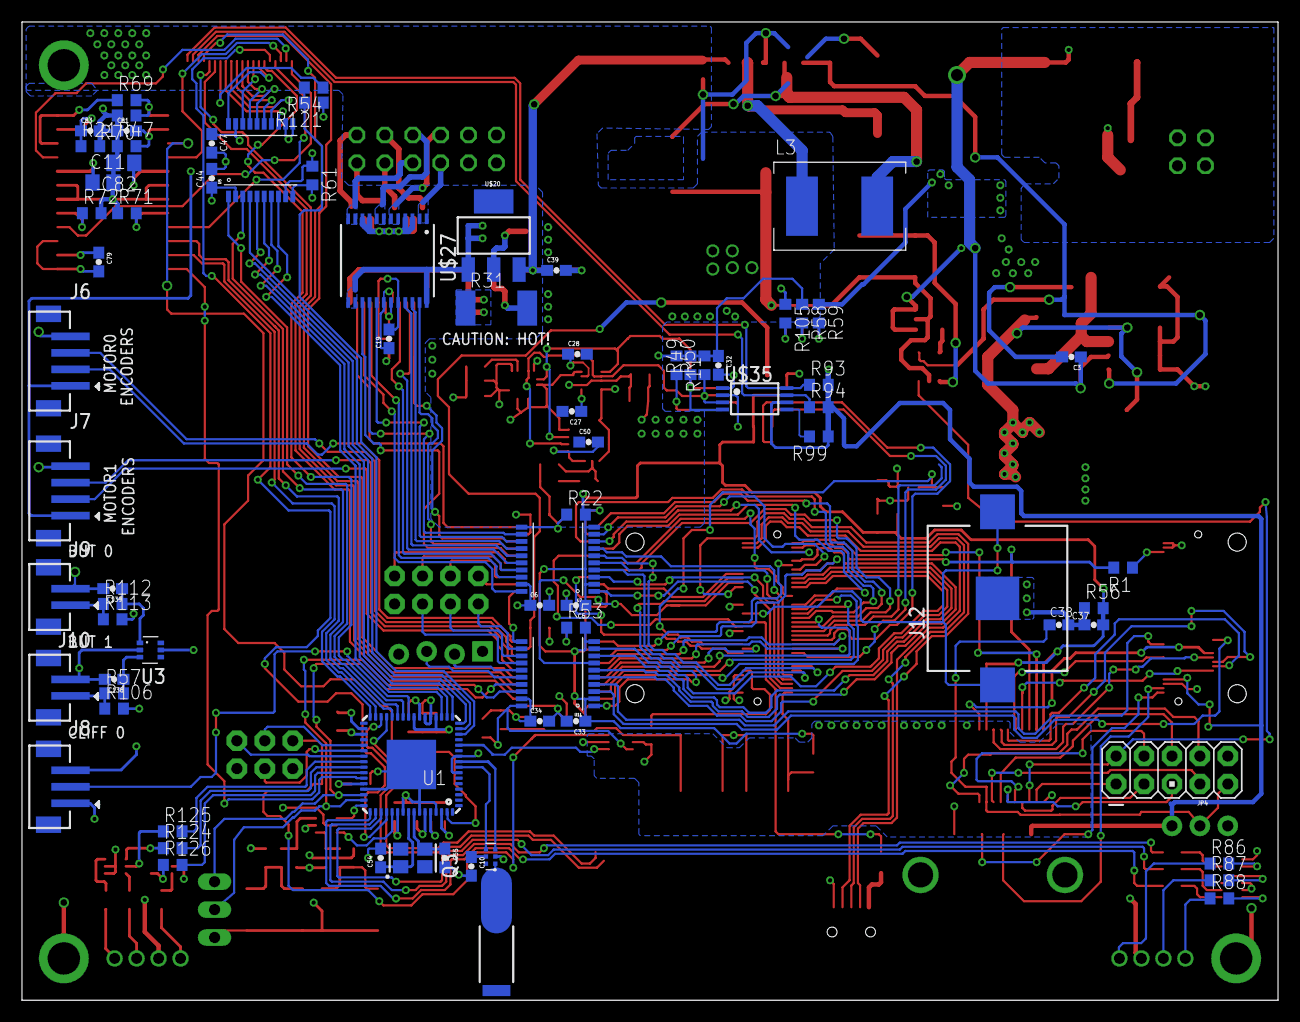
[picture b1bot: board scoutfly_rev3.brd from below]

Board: 4 copper layers, 114.3 x 89.0 mm, 179 parts (77 on the bottom side), 214 nets.

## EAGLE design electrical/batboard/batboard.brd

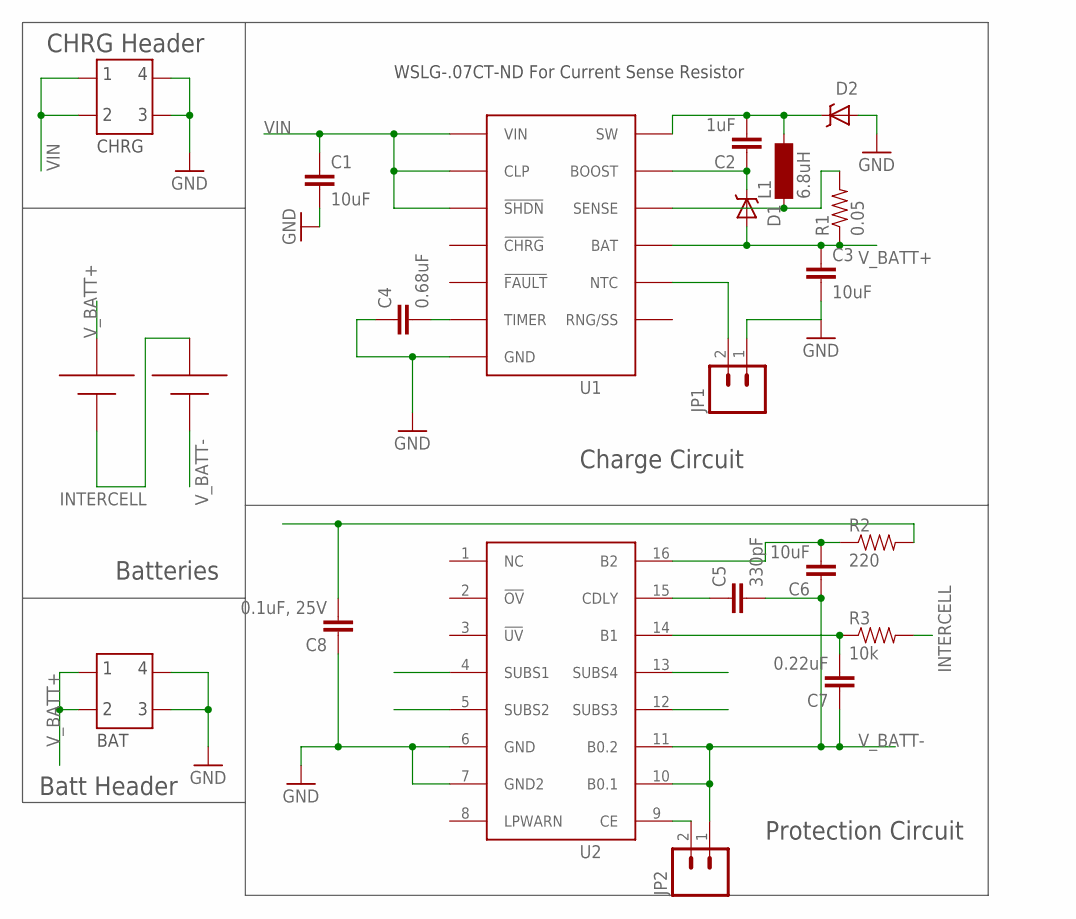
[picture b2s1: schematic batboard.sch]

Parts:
BAT: C-GRID-71308; 4HEAD_MOLEX_C71308
C1, C3, C6: 10uF; 0805
C2: 1uF; 0805
C4: 0.68uF; 0805
C5: 330pF; 0805
C7: 0.22uF; 0805
C8: 0.1uF, 25V; 0805
CHRG: C-GRID-71308; 4HEAD_MOLEX_C71308
D1, D2: DIODE-SCHOTTKY_; SMA-DIODE
JP1, JP2: M02PTH; 1X02
L1: 6.8uH; SM-1206
R1: 0.05; R2512
R2: 220; 0603-RES
R3: 10k; 0603-RES
U1: LT3650; 12-MSOP
U2: UCC3911; SOIC-16
U$1: BK-18650-PC4; 18650-PC4

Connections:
GND: BAT.3, BAT.4, C1.2, C3.2, C4.1, C8.1, CHRG.3, CHRG.4, D2.A, JP1.1, U1.GND, U2.6 (GND), U2.7 (GND2)
HSINK: U2.4 (SUBS1), U2.5 (SUBS2), U2.12 (SUBS3), U2.13 (SUBS4)
INTERCELL: R3.2, U$1.+2, U$1.-1
unnamed: JP2.2, U2.9 (CE)
unnamed: C2.1, D1.C, U1.11 (BOOST)
unnamed: JP1.2, U1.8 (NTC)
unnamed: C4.2, U1.6 (TIMER)
unnamed: C2.2, D2.C, L1.2, U1.12 (SW)
unnamed: L1.1, R1.2, U1.10 (SENSE)
unnamed: C5.1, U2.15 (CDLY)
unnamed: C6.2, R2.1, U2.16 (B2)
unnamed: C7.2, R3.1, U2.14 (B1)
VIN: C1.1, CHRG.1, CHRG.2, U1.1 (VIN), U1.2 (CLP), U1.3 (!SHDN)
V_BATT+: BAT.1, BAT.2, C3.1, C8.2, D1.A, R1.1, R2.2, U1.9 (BAT), U$1.+1
V_BATT-: C5.2, C6.1, C7.1, JP2.1, U2.10 (B0.1), U2.11 (B0.2), U$1.-2

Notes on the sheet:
Batteries
Batt Header
CHRG Header
WSLG-.07CT-ND For Current Sense Resistor
Charge Circuit
Protection Circuit

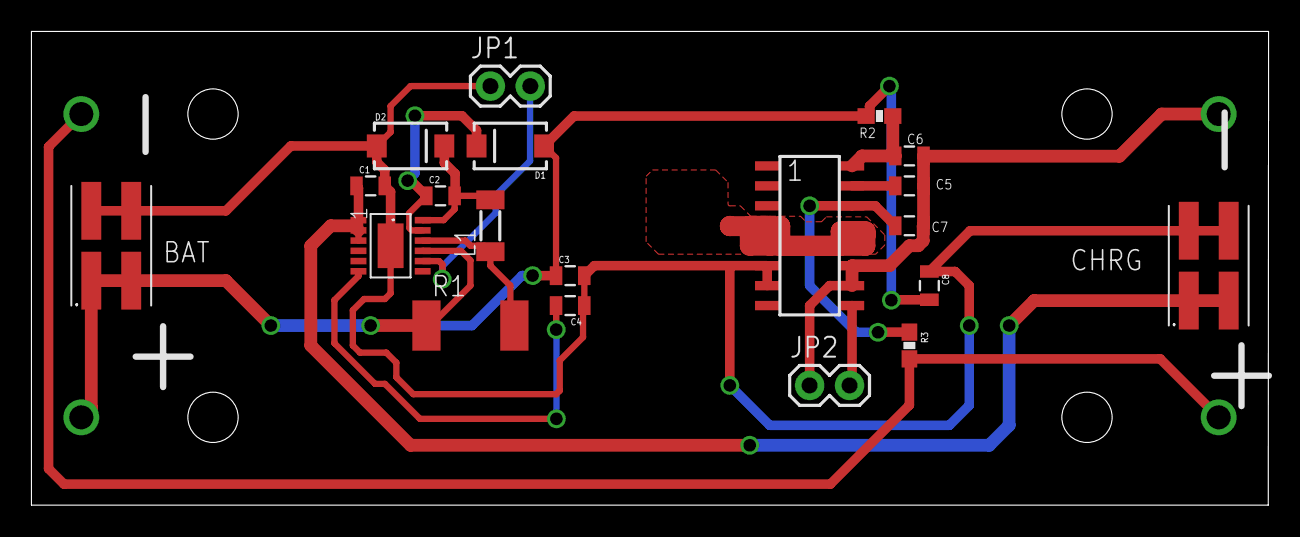
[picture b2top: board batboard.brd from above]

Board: 2 copper layers, 78.7 x 30.1 mm, 21 parts (1 on the bottom side), 15 nets.

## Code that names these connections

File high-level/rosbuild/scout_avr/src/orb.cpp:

extern "C" {
#include <avr/io.h>
#include <util/delay.h>
}
#include "orb.h"

void orb_init() {

  /* set pins to output mode */
	DDRB |= _BV(PB4) | _BV(PB5) | _BV(PB6);
  DDRE |= _BV(PE3) | _BV(PE4) | _BV(PE5);

  orb_set0(0, 0, 0);
  //orb_set1(0, 0, 0);
  orb_set1(0, 255, 255);
  	
	/* timer 2 */
  TCCR2A |= _BV(COM2A1) | _BV(COM2A0) | _BV(WGM20);
	TCCR2B |= _BV(CS21);

	/* timer 1 */
	TCCR1A |= _BV(COM1A1) | _BV(COM1A0) |  _BV(COM1B1) | _BV(COM1B0) |_BV(WGM10);
	TCCR1B |= _BV(CS11);

	/* timer 3 */
  TCCR3A |= _BV(COM3A1) | _BV(COM3A0) | _BV(COM3B1) | _BV(COM3B0) | _BV(COM3C1)
    | _BV(COM3C0) | _BV(WGM30);
	TCCR3B |= _BV(CS31);
}

void orb_set0(unsigned char r, unsigned char g, unsigned char b) {
	OCR1B = r;
	OCR2A = g;
	OCR1A = b;
}

void orb_set1(unsigned char r, unsigned char g, unsigned char b) {
	OCR3B = r;
	OCR3C = g;
	OCR3A = b;
}

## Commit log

2014-09-25 Add subteam meeting times
2014-10-16 Added subgroup leader names to README
2014-10-18 Add Udoo I2C example
2014-11-08 Adding test arduino sketches
2015-02-05 Create high-level
2015-02-06 added actual, real-live content to the project
2015-02-12 Created readme to keep track of to-do list
2015-02-19 Add electrical
2015-02-19 Added Odometry
2015-03-04 reorganized and added misty's catkin build
2015-03-05 added catkinized project
2015-03-05 reorganized, added catkinized project
2015-03-06 Added script for compiling packages
2015-03-26 disambiguated script name
2015-03-26 removed old script

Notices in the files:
parts and their libraries:
SparkFun-Capacitors: Licensing: CC v3.0 Share-Alike You are welcome to use this library for commercial purposes.
